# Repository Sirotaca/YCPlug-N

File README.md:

# YCPlug Type N
Compact S-Video adapter for the SNES/SFC-style AV multi-out.

For NTSC consoles, close JP1 and JP2 and do not populate R1, R2, C1, or C2. For PAL consoles, leave JP1 and JP2 open and populate R1, R2, C1, and C2.

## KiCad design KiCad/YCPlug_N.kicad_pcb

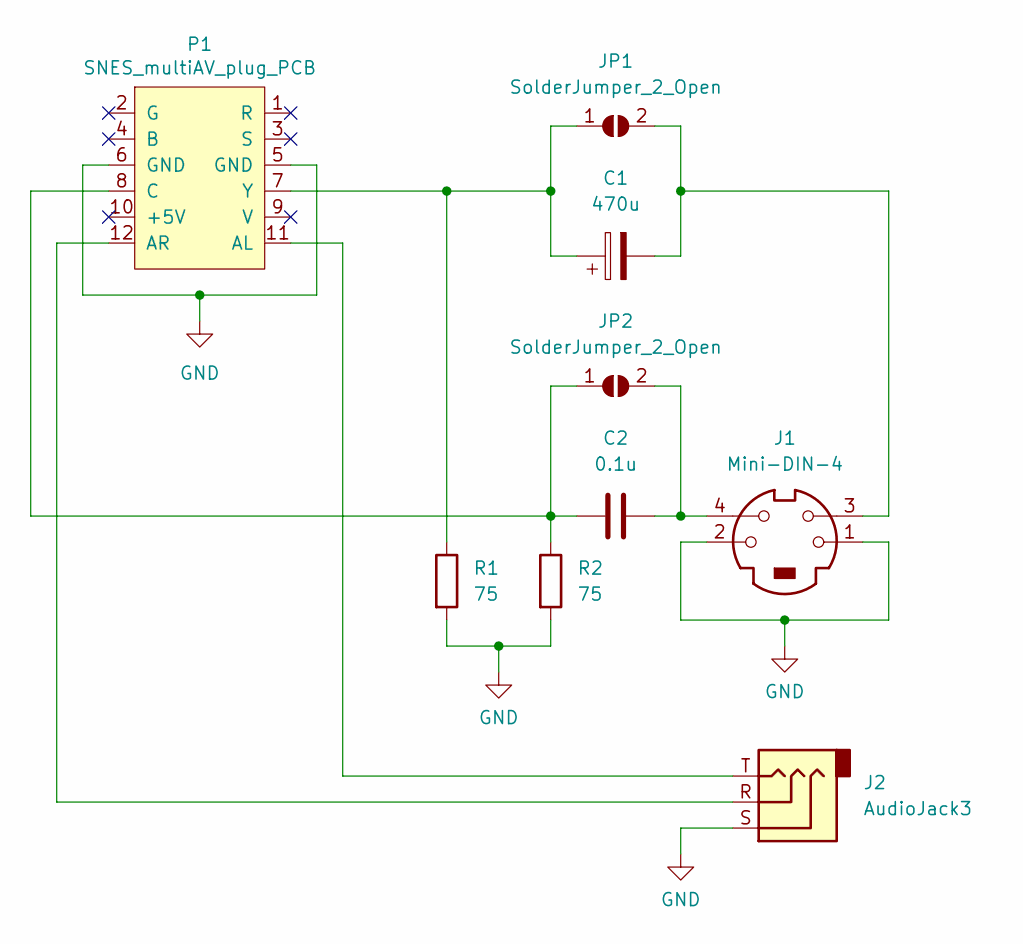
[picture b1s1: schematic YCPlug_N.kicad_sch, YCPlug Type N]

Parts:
C1: 470u; CP_EIA-7343-30_AVX-N_Pad2.25x2.55mm_HandSolder
C2: 0.1u; C_0805_2012Metric_Pad1.18x1.45mm_HandSolder
J1: Mini-DIN-4; MD-40S
J2: AudioJack3; Jack_3.5mm_CUI_SJ1-3533NG_Horizontal
JP1, JP2: SolderJumper_2_Open; SolderJumper-2_P1.3mm_Open_TrianglePad1.0x1.5mm
P1: SNES_multiAV_plug_PCB
R1, R2: 75; R_0805_2012Metric_Pad1.20x1.40mm_HandSolder

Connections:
GND: J1.1, J1.2, J2.S, P1.5 (GND), P1.6 (GND), R1.2, R2.2
unnamed: C1.1, JP1.1 (A), P1.7 (Y), R1.1
unnamed: C1.2, J1.3, JP1.2 (B)
unnamed: C2.1, JP2.1 (A), P1.8 (C), R2.1
unnamed: C2.2, J1.4, JP2.2 (B)
unnamed: J2.R, P1.12 (AR)
unnamed: J2.T, P1.11 (AL)

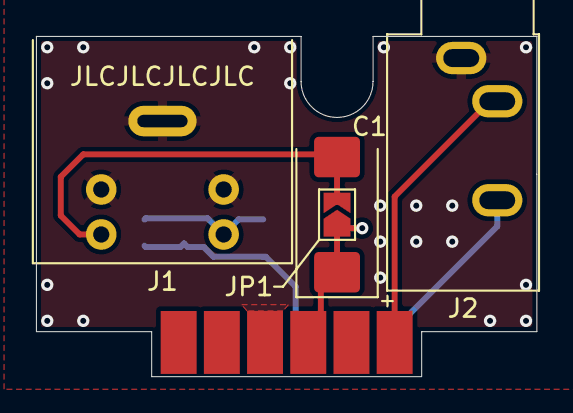
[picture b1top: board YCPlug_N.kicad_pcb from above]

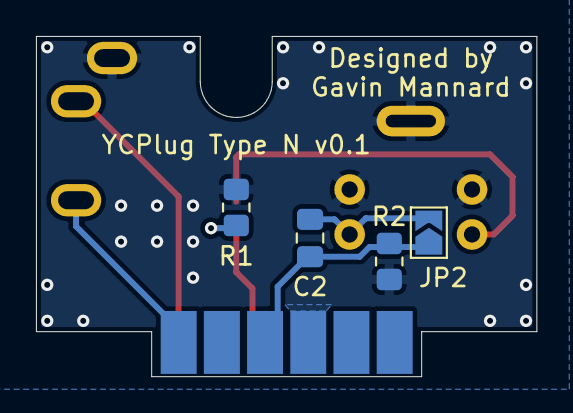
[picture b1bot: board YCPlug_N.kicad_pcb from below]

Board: 2 copper layers, 27.8 x 18.9 mm, 9 parts (4 on the bottom side), 7 nets.

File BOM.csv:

"Reference","Value","Datasheet","Footprint","Qty","DNP"
"C1","470u","~","Capacitor_Tantalum_SMD:CP_EIA-7343-30_AVX-N_Pad2.25x2.55mm_HandSolder","1",""
"C2","0.1u","~","Capacitor_SMD:C_0805_2012Metric_Pad1.18x1.45mm_HandSolder","1",""
"J1","Mini-DIN-4","http://service.powerdynamics.com/ec/Catalog17/Section%2011.pdf","retro_gaming:MD-40S","1",""
"J2","AudioJack3","~","Connector_Audio:Jack_3.5mm_CUI_SJ1-3533NG_Horizontal","1",""
"JP1,JP2","SolderJumper_2_Open","~","Jumper:SolderJumper-2_P1.3mm_Open_TrianglePad1.0x1.5mm","2",""
"P1","SNES_multiAV_plug_PCB","","retro_gaming:SNES_multiAV_plug_PCB","1",""
"R1,R2","75","~","Resistor_SMD:R_0805_2012Metric_Pad1.20x1.40mm_HandSolder","2",""
